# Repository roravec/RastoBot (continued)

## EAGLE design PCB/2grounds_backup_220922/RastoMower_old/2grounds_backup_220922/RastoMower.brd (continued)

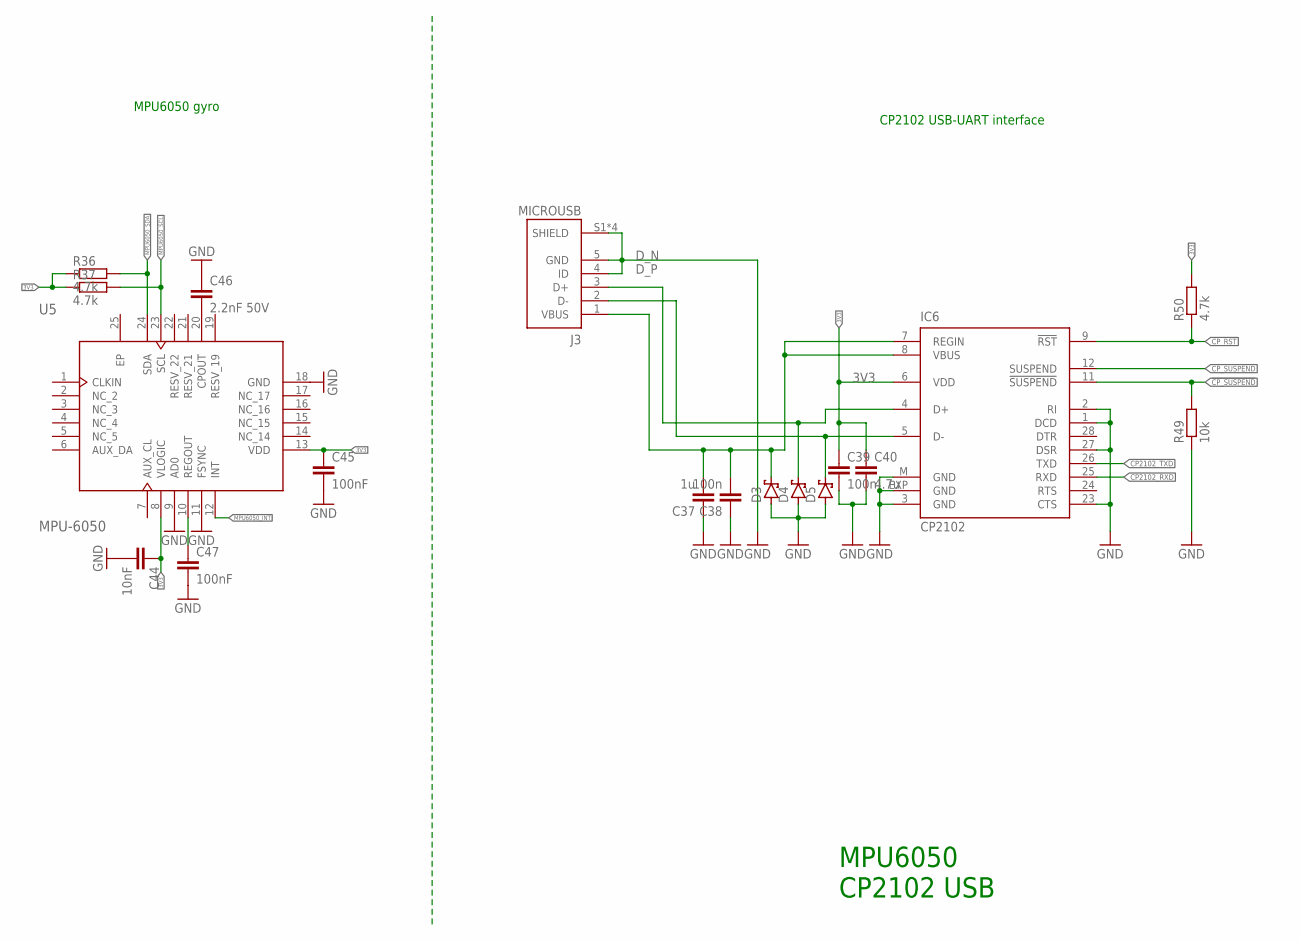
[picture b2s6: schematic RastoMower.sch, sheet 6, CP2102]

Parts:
C37: 1u; C0603
C38, C39: 100n; C0603
C40: 4.7u; C0603
C44: 10nF; C0603
C45, C47: 100nF; C0603
C46: 2.2nF 50V; C0603
D3, D4, D5: BAT60J; SOD323_ST
IC6: CP2102; MLP28
J3: MICROUSB; MOLEX_47642-0001
R36, R37, R50: 4.7k; R0603
R49: 10k; R0603
U5: MPU-6050; 24-VFQFN

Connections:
!CP_SUSPEND: IC6.11 (!SUSPEND), R49.2
CP2102_RXD: IC6.25 (RXD); also elsewhere on the board
CP2102_TXD: IC6.26 (TXD); also elsewhere on the board
CP_RST: IC6.9 (!RST), R50.1
CP_SUSPEND: IC6.12 (SUSPEND)
D_N: D5.C, IC6.5 (D-), J3.2 (D-)
D_P: D4.C, IC6.4 (D+), J3.3 (D+)
EP: U5.25 (EP)
MPU6050_INT: U5.12 (INT)
MPU6050_SCL: R37.2, U5.23 (SCL); also elsewhere on the board
MPU6050_SDA: R36.2, U5.24 (SDA); also elsewhere on the board
unnamed: C37.2, C38.2, D3.C, IC6.7 (REGIN), IC6.8 (VBUS), J3.1 (VBUS)
unnamed: C46.2, U5.20 (CPOUT)
unnamed: C47.1, U5.10 (REGOUT)

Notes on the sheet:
MPU6050 CP2102 USB
MPU6050 gyro
CP2102 USB-UART interface

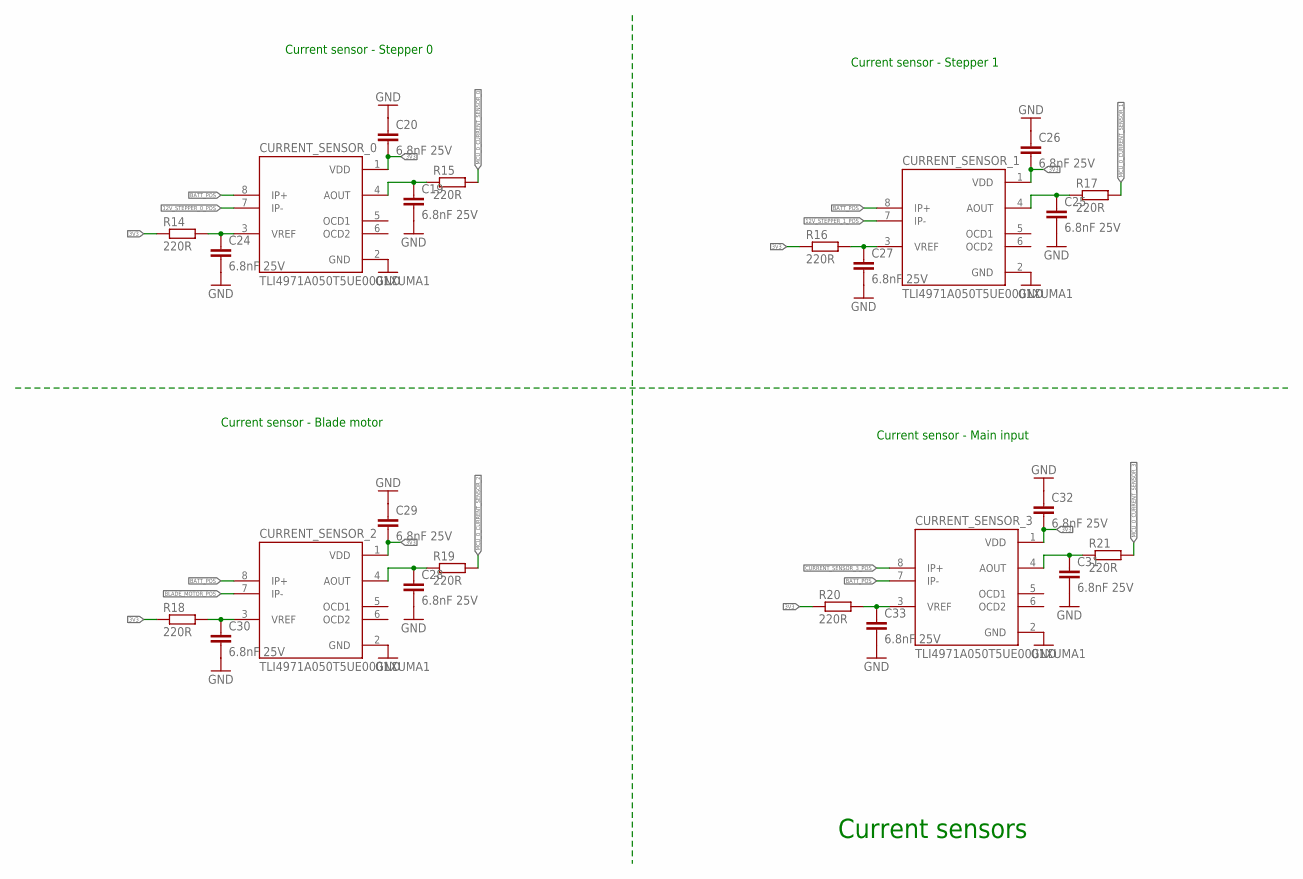
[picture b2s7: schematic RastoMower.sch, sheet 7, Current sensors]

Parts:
C19, C20, C24, C25, C26, C27, C28, C29, C30, C31, C32, C33: 6.8nF 25V; C0603
CURRENT_SENSOR_0, CURRENT_SENSOR_1, CURRENT_SENSOR_2, CURRENT_SENSOR_3: TLI4971A050T5UE0001XUMA1; IC_TLI4971A050T5UE0001XUMA1
R14, R15, R16, R17, R18, R19, R20, R21: 220R; R0805

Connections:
12V_STEPPER_0_POS: CURRENT_SENSOR_0.7 (IP-); also elsewhere on the board
12V_STEPPER_1_POS: CURRENT_SENSOR_1.7 (IP-); also elsewhere on the board
BLADE_MOTOR_POS: CURRENT_SENSOR_2.7 (IP-); also elsewhere on the board
CURRENT_SENSOR_3_POS: CURRENT_SENSOR_3.8 (IP+); also elsewhere on the board
MCU_0_CURRENT_SENSOR_0: R15.2; also elsewhere on the board
MCU_0_CURRENT_SENSOR_1: R17.2; also elsewhere on the board
MCU_0_CURRENT_SENSOR_2: R19.2; also elsewhere on the board
MCU_0_CURRENT_SENSOR_3: R21.2; also elsewhere on the board
unnamed: C19.1, CURRENT_SENSOR_0.4 (AOUT), R15.1
unnamed: C27.1, CURRENT_SENSOR_1.3 (VREF), R16.2
unnamed: C25.1, CURRENT_SENSOR_1.4 (AOUT), R17.1
unnamed: C24.1, CURRENT_SENSOR_0.3 (VREF), R14.2
unnamed: C30.1, CURRENT_SENSOR_2.3 (VREF), R18.2
unnamed: C28.1, CURRENT_SENSOR_2.4 (AOUT), R19.1
unnamed: C33.1, CURRENT_SENSOR_3.3 (VREF), R20.2
unnamed: C31.1, CURRENT_SENSOR_3.4 (AOUT), R21.1

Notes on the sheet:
Current sensors
Current sensor - Stepper 0
Current sensor - Stepper 1
Current sensor - Blade motor
Current sensor - Main input

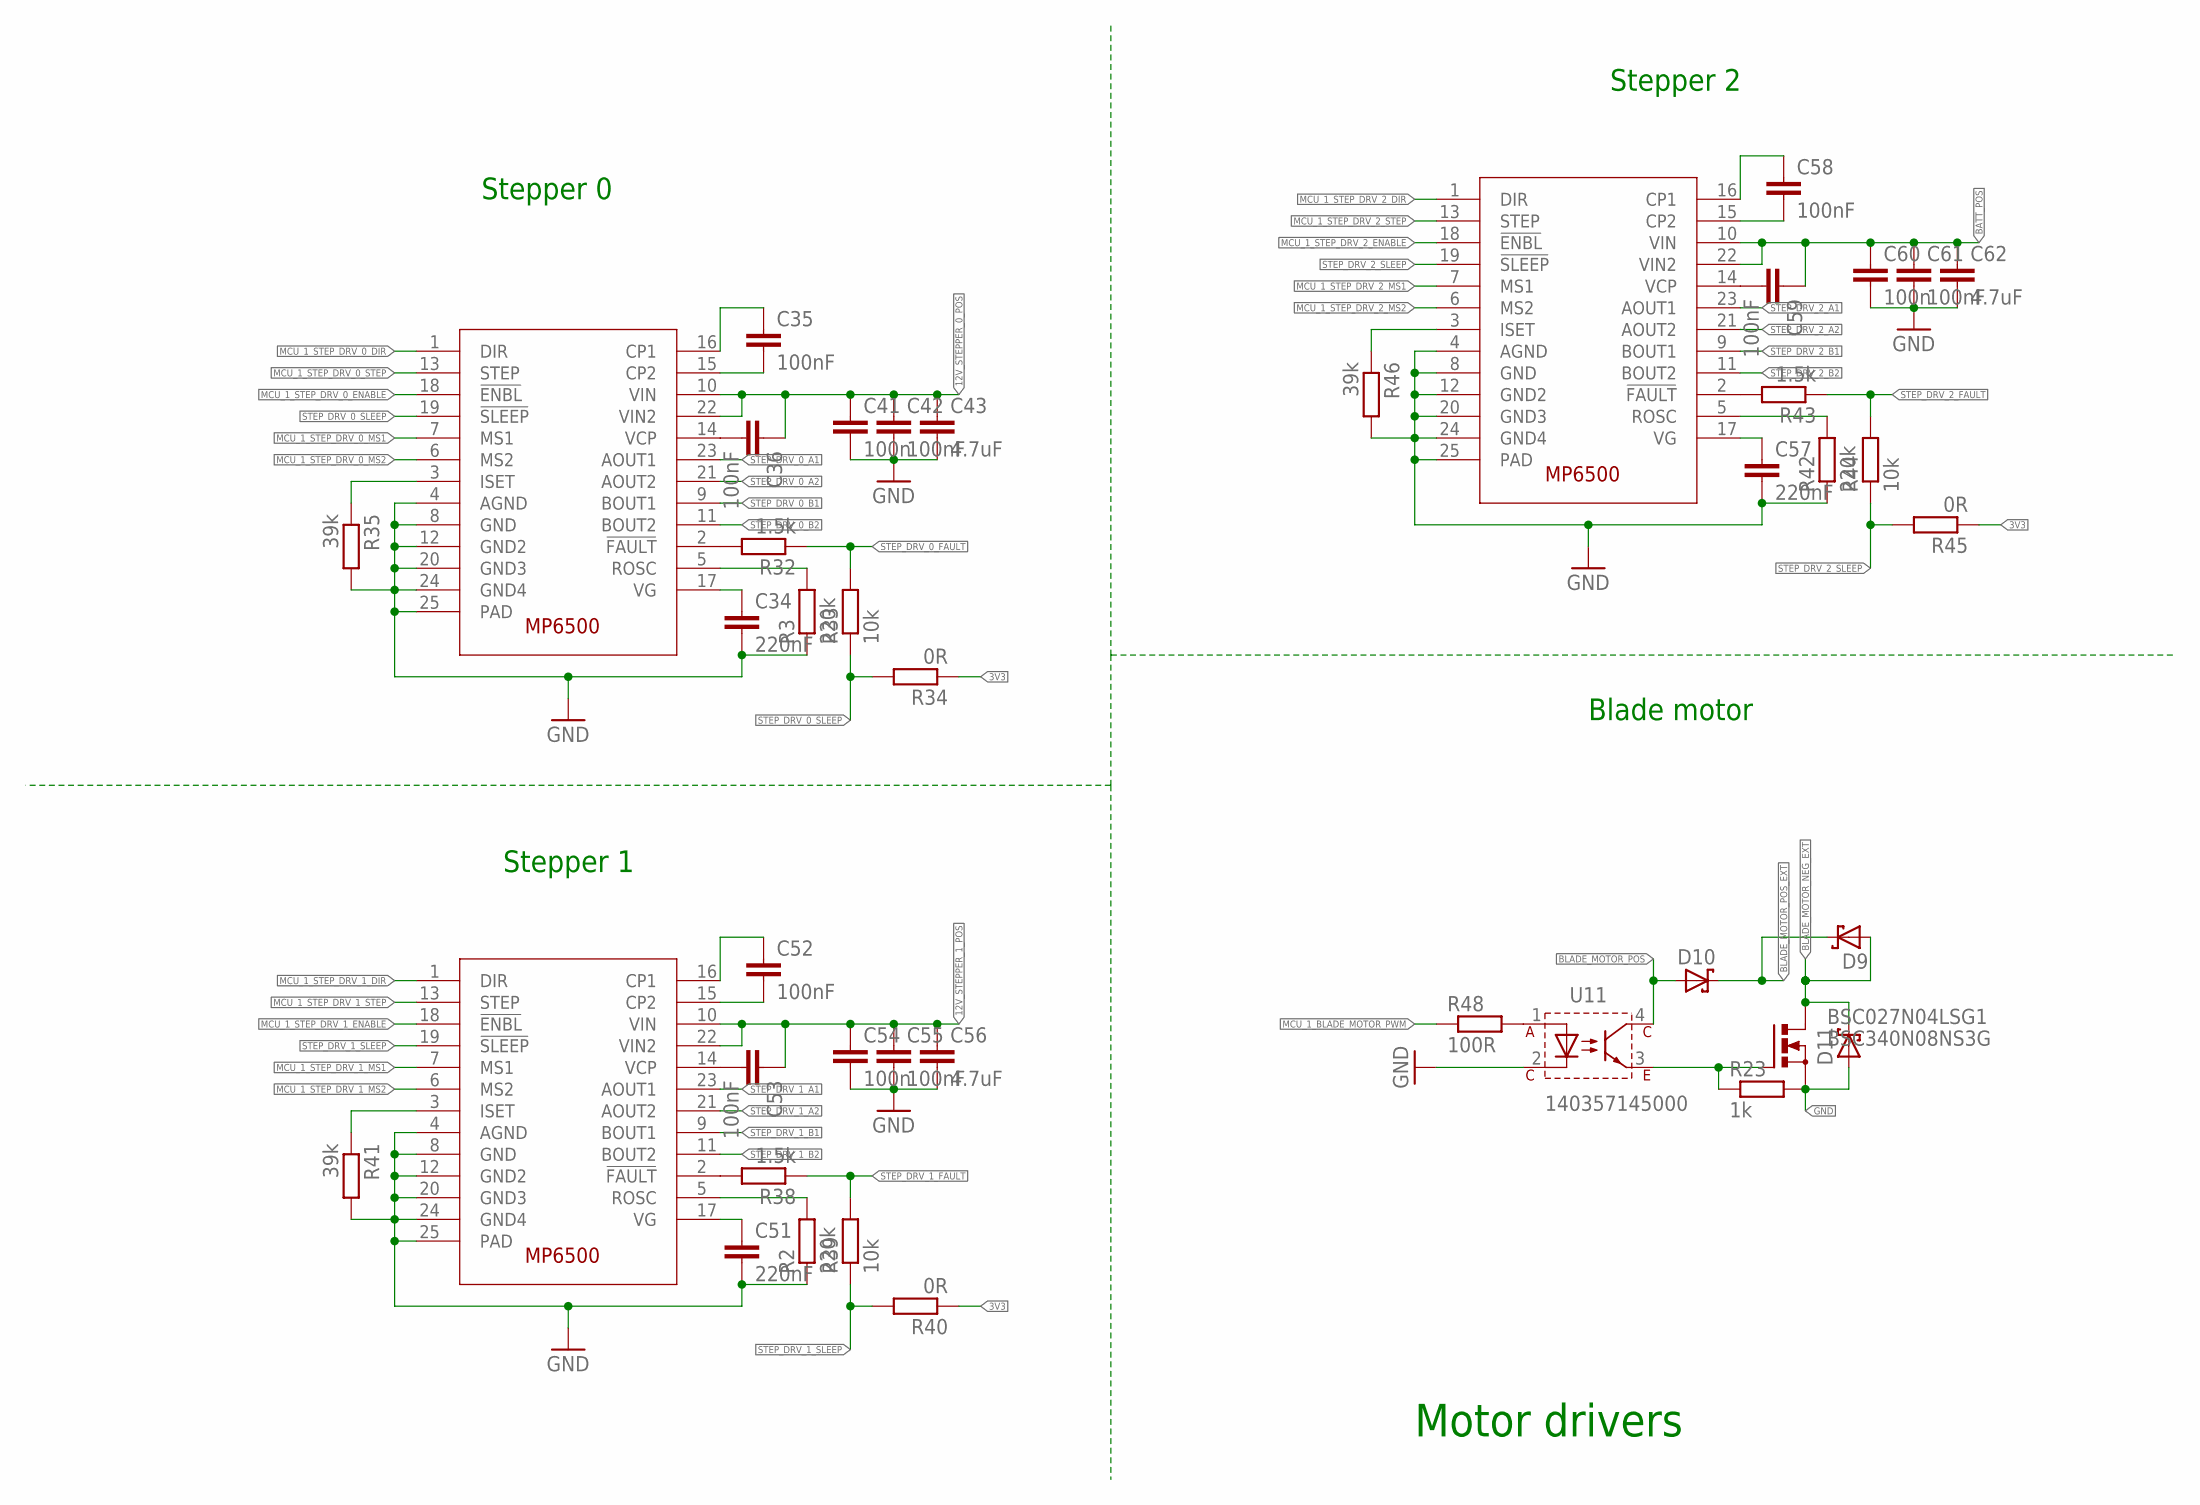
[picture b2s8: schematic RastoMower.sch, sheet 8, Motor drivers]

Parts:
BSC027N04LSG1: BSC340N08NS3G; PG-TDSON-8
C34, C51, C57: 220nF; C0603
C35, C36, C42, C52, C53, C55, C58, C59, C61: 100nF; C0603
C41, C54, C60: 100n; C0603
C43, C56, C62: 4.7uF; C0603
D9, D10, D11: SCHOTTKY-DIODEAG; AG
R2, R3, R42: 220k; R0603
R23: 1k; R0805
R32, R38, R43: 1.5k; R0603
R33, R39, R44: 10k; R0603
R34, R40, R45: 0R; R0603
R35, R41, R46: 39k; R0603
R48: 100R; R0805
U11: 140357145000; WL-OCPT_SOP4
U$1, U$2, U$3: MP6500; QFN65P500X500X100-25N

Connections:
12V_STEPPER_0_POS: C36.1, C41.1, C42.1, C43.1, U$1.10 (VIN), U$1.22 (VIN2); also elsewhere on the board
12V_STEPPER_1_POS: C53.1, C54.1, C55.1, C56.1, U$2.10 (VIN), U$2.22 (VIN2); also elsewhere on the board
BLADE_MOTOR_NEG_EXT: BSC027N04LSG1.5 (D), BSC027N04LSG1.6 (D), BSC027N04LSG1.7 (D), BSC027N04LSG1.8 (D), D9.A, D11.C; also elsewhere on the board
BLADE_MOTOR_POS: D10.A, U11.4; also elsewhere on the board
BLADE_MOTOR_POS_EXT: D9.C, D10.C; also elsewhere on the board
MCU_1_BLADE_MOTOR_PWM: R48.1; also elsewhere on the board
MCU_1_STEP_DRV_0_DIR: U$1.1 (DIR); also elsewhere on the board
MCU_1_STEP_DRV_0_ENABLE: U$1.18 (!ENBL); also elsewhere on the board
MCU_1_STEP_DRV_0_MS1: U$1.7 (MS1); also elsewhere on the board
MCU_1_STEP_DRV_0_MS2: U$1.6 (MS2); also elsewhere on the board
MCU_1_STEP_DRV_0_STEP: U$1.13 (STEP); also elsewhere on the board
MCU_1_STEP_DRV_1_DIR: U$2.1 (DIR); also elsewhere on the board
MCU_1_STEP_DRV_1_ENABLE: U$2.18 (!ENBL); also elsewhere on the board
MCU_1_STEP_DRV_1_MS1: U$2.7 (MS1); also elsewhere on the board
MCU_1_STEP_DRV_1_MS2: U$2.6 (MS2); also elsewhere on the board
MCU_1_STEP_DRV_1_STEP: U$2.13 (STEP); also elsewhere on the board
MCU_1_STEP_DRV_2_DIR: U$3.1 (DIR); also elsewhere on the board
MCU_1_STEP_DRV_2_ENABLE: U$3.18 (!ENBL); also elsewhere on the board
MCU_1_STEP_DRV_2_MS1: U$3.7 (MS1); also elsewhere on the board
MCU_1_STEP_DRV_2_MS2: U$3.6 (MS2); also elsewhere on the board
MCU_1_STEP_DRV_2_STEP: U$3.13 (STEP); also elsewhere on the board
unnamed: C34.1, U$1.17 (VG)
unnamed: R3.2, U$1.5 (ROSC)
unnamed: R48.2, U11.1
unnamed: BSC027N04LSG1.4 (G), R23.1, U11.3
unnamed: C35.2, U$1.15 (CP2)
unnamed: C35.1, U$1.16 (CP1)
unnamed: R32.2, U$1.2 (!FAULT)
unnamed: C36.2, U$1.14 (VCP)
unnamed: C51.1, U$2.17 (VG)
unnamed: R35.1, U$1.3 (ISET)
unnamed: R2.2, U$2.5 (ROSC)
unnamed: C52.2, U$2.15 (CP2)
unnamed: C52.1, U$2.16 (CP1)
unnamed: C53.2, U$2.14 (VCP)
unnamed: R41.1, U$2.3 (ISET)
unnamed: R38.2, U$2.2 (!FAULT)
unnamed: C57.1, U$3.17 (VG)
unnamed: R42.2, U$3.5 (ROSC)
unnamed: C58.2, U$3.15 (CP2)
unnamed: C58.1, U$3.16 (CP1)
unnamed: C59.2, U$3.14 (VCP)
unnamed: R46.1, U$3.3 (ISET)
unnamed: R43.2, U$3.2 (!FAULT)
STEP_DRV_0_A1: U$1.23 (AOUT1); also elsewhere on the board
STEP_DRV_0_A2: U$1.21 (AOUT2); also elsewhere on the board
STEP_DRV_0_B1: U$1.9 (BOUT1); also elsewhere on the board
STEP_DRV_0_B2: U$1.11 (BOUT2); also elsewhere on the board
STEP_DRV_0_FAULT: R32.1, R33.2
STEP_DRV_0_SLEEP: R33.1, R34.2, U$1.19 (!SLEEP)
STEP_DRV_1_A1: U$2.23 (AOUT1); also elsewhere on the board
STEP_DRV_1_A2: U$2.21 (AOUT2); also elsewhere on the board
STEP_DRV_1_B1: U$2.9 (BOUT1); also elsewhere on the board
STEP_DRV_1_B2: U$2.11 (BOUT2); also elsewhere on the board
STEP_DRV_1_FAULT: R38.1, R39.2
STEP_DRV_1_SLEEP: R39.1, R40.2, U$2.19 (!SLEEP)
STEP_DRV_2_A1: U$3.23 (AOUT1); also elsewhere on the board
STEP_DRV_2_A2: U$3.21 (AOUT2); also elsewhere on the board
STEP_DRV_2_B1: U$3.9 (BOUT1); also elsewhere on the board
STEP_DRV_2_B2: U$3.11 (BOUT2); also elsewhere on the board
STEP_DRV_2_FAULT: R43.1, R44.2
STEP_DRV_2_SLEEP: R44.1, R45.2, U$3.19 (!SLEEP)

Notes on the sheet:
Stepper 0
Stepper 1
Stepper 2
Blade motor
Motor drivers

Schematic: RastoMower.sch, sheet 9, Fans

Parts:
BSC027N04LSG3, BSC027N04LSG4, BSC027N04LSG5, BSC027N04LSG6, BSC027N04LSG7: BSC340N08NS3G; PG-TDSON-8
JP10: FAN_0; 1X02
JP11: FAN_1; 1X02
JP12: FAN_2; 1X02
JP13: FAN_3; 1X02
JP25: EMERGENCY LIGHT; 1X02
R22, R51, R52, R53, R119: 200R; R0805
R63, R65, R67, R68, R76: 1k; R0805
U4, U6, U7, U8, U12: 140357145000; WL-OCPT_SOP4

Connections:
MCU_0_EMERGENCY_LIGHT: R119.1; also elsewhere on the board
MCU_0_FAN_0: R22.1; also elsewhere on the board
MCU_0_FAN_1: R51.1; also elsewhere on the board
MCU_0_FAN_2: R53.1; also elsewhere on the board
MCU_0_FAN_3: R52.1; also elsewhere on the board
unnamed: BSC027N04LSG3.4 (G), R68.1, U12.3
unnamed: BSC027N04LSG3.5 (D), BSC027N04LSG3.6 (D), BSC027N04LSG3.7 (D), BSC027N04LSG3.8 (D), JP25.2
unnamed: R119.2, U12.1
unnamed: R22.2, U4.1
unnamed: BSC027N04LSG4.5 (D), BSC027N04LSG4.6 (D), BSC027N04LSG4.7 (D), BSC027N04LSG4.8 (D), JP10.2
unnamed: R51.2, U6.1
unnamed: R52.2, U8.1
unnamed: BSC027N04LSG4.4 (G), R76.1, U4.3
unnamed: BSC027N04LSG5.4 (G), R63.1, U6.3
unnamed: BSC027N04LSG5.5 (D), BSC027N04LSG5.6 (D), BSC027N04LSG5.7 (D), BSC027N04LSG5.8 (D), JP11.2
unnamed: R53.2, U7.1
unnamed: BSC027N04LSG6.4 (G), R65.1, U7.3
unnamed: BSC027N04LSG6.5 (D), BSC027N04LSG6.6 (D), BSC027N04LSG6.7 (D), BSC027N04LSG6.8 (D), JP12.2
unnamed: BSC027N04LSG7.4 (G), R67.1, U8.3
unnamed: BSC027N04LSG7.5 (D), BSC027N04LSG7.6 (D), BSC027N04LSG7.7 (D), BSC027N04LSG7.8 (D), JP13.2

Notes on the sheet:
Fan_0
Fan_1
Fan_2
Fan_3
Fan drivers Emergency light switch
Emergency light

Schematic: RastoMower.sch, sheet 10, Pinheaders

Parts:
BSC027N04LSG2: BSC340N08NS3G; PG-TDSON-8
C63, C64, C65, C66: 1u; C0603
D2: 3V3; SOD80C
JP1: GPS MODULE; 1X05
JP2: STEPPER_0; 1X04
JP3: STEPPER_1; 1X04
JP4: STEPPER_2; 1X04
JP5: LIDAR; 1X08
JP6: RAIN SENSOR; 1X02
JP7: BLADE MOTOR; 1X04
JP8: LIMIT SWITCH UP; 1X02
JP9: LIMIT SWITCH DOWN; 1X02
JP14: TEMP SENSOR 0; 1X03
JP15: TEMP SENSOR 1; 1X03
JP16: TEMP SENSOR 2; 1X03
JP17: TEMP SENSOR 3; 1X03
JP22: PER.WIRE SENSE; 1X04
JP24: PHOTORESISTOR LDR5549; 1X02
JP30: LIMIT_SWITCH_UPPER_MAGNETIC; 1X03
JP31: LIMIT_SWITCH_BOTTOM_MAGNETIC; 1X03
R4, R54: 1k; R0805
R55, R64: 500k; R0805
R56, R58, R59, R60, R107, R108, R109, R110: 10k; R0805
R57, R66: 10R; R0805
R62: 200R; R0805
R69, R70, R71, R72: 5k; R0805
U10: 140357145000; WL-OCPT_SOP4

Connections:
BLADE_MOTOR_NEG_EXT: JP7.3, JP7.4; also elsewhere on the board
BLADE_MOTOR_POS_EXT: JP7.1, JP7.2; also elsewhere on the board
GPS_PPS: JP1.5
GPS_RXD: JP1.4; also elsewhere on the board
GPS_TXD: JP1.3; also elsewhere on the board
LIDAR_RX: JP5.4; also elsewhere on the board
LIDAR_TX: JP5.7; also elsewhere on the board
LIMIT_SWITCH_BOTTOM_MAGNET: R108.1; also elsewhere on the board
LIMIT_SWITCH_BOTTOM_MECHANICAL: R60.1; also elsewhere on the board
LIMIT_SWITCH_UPPER_MAGNET: R107.1; also elsewhere on the board
LIMIT_SWITCH_UPPER_MECHANICAL: R59.1; also elsewhere on the board
MCU_0_LIGHT_SENSOR: R66.1; also elsewhere on the board
MCU_0_TEMP_SENSOR_0: JP14.2, R69.1; also elsewhere on the board
MCU_0_TEMP_SENSOR_1: JP15.2, R70.1; also elsewhere on the board
MCU_0_TEMP_SENSOR_2: JP16.2, R71.1; also elsewhere on the board
MCU_0_TEMP_SENSOR_3: JP17.2, R72.1; also elsewhere on the board
MCU_2_LIDAR_ENABLE: R62.1; also elsewhere on the board
unnamed: JP22.2, R4.2
unnamed: BSC027N04LSG2.5 (D), BSC027N04LSG2.6 (D), BSC027N04LSG2.7 (D), BSC027N04LSG2.8 (D), JP5.5
unnamed: JP8.2, R56.2, R59.2
unnamed: JP9.2, R58.2, R60.2
unnamed: BSC027N04LSG2.4 (G), R54.1, U10.3
unnamed: R62.2, U10.1
unnamed: JP31.2, R108.2, R109.2
unnamed: JP30.2, R107.2, R110.2
PERIMETER_WIRE_SENSE: D2.A, R4.1; also elsewhere on the board
STEP_DRV_0_A1: JP2.1; also elsewhere on the board
STEP_DRV_0_A2: JP2.2; also elsewhere on the board
STEP_DRV_0_B1: JP2.3; also elsewhere on the board
STEP_DRV_0_B2: JP2.4; also elsewhere on the board
STEP_DRV_1_A1: JP3.1; also elsewhere on the board
STEP_DRV_1_A2: JP3.2; also elsewhere on the board
STEP_DRV_1_B1: JP3.3; also elsewhere on the board
STEP_DRV_1_B2: JP3.4; also elsewhere on the board
STEP_DRV_2_A1: JP4.1; also elsewhere on the board
STEP_DRV_2_A2: JP4.2; also elsewhere on the board
STEP_DRV_2_B1: JP4.3; also elsewhere on the board
STEP_DRV_2_B2: JP4.4; also elsewhere on the board

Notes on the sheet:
GPS TXD to MCU RX!
Resistance is between 10M (dry) to less than 1M (fully wet)
Limit switch UP
Limit switch BOTTOM
Blade motor
Stepper_0
Stepper_1
Stepper_2
GPS
Rain sensor
Mechanical limit switches
Temperature sensor DHT11
Perimeter wire sense
Lidar
Magnetic limit switches
Pinheaders
Resistance is between 10M (dark) to less than 100k (daylight)
Light sensor

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
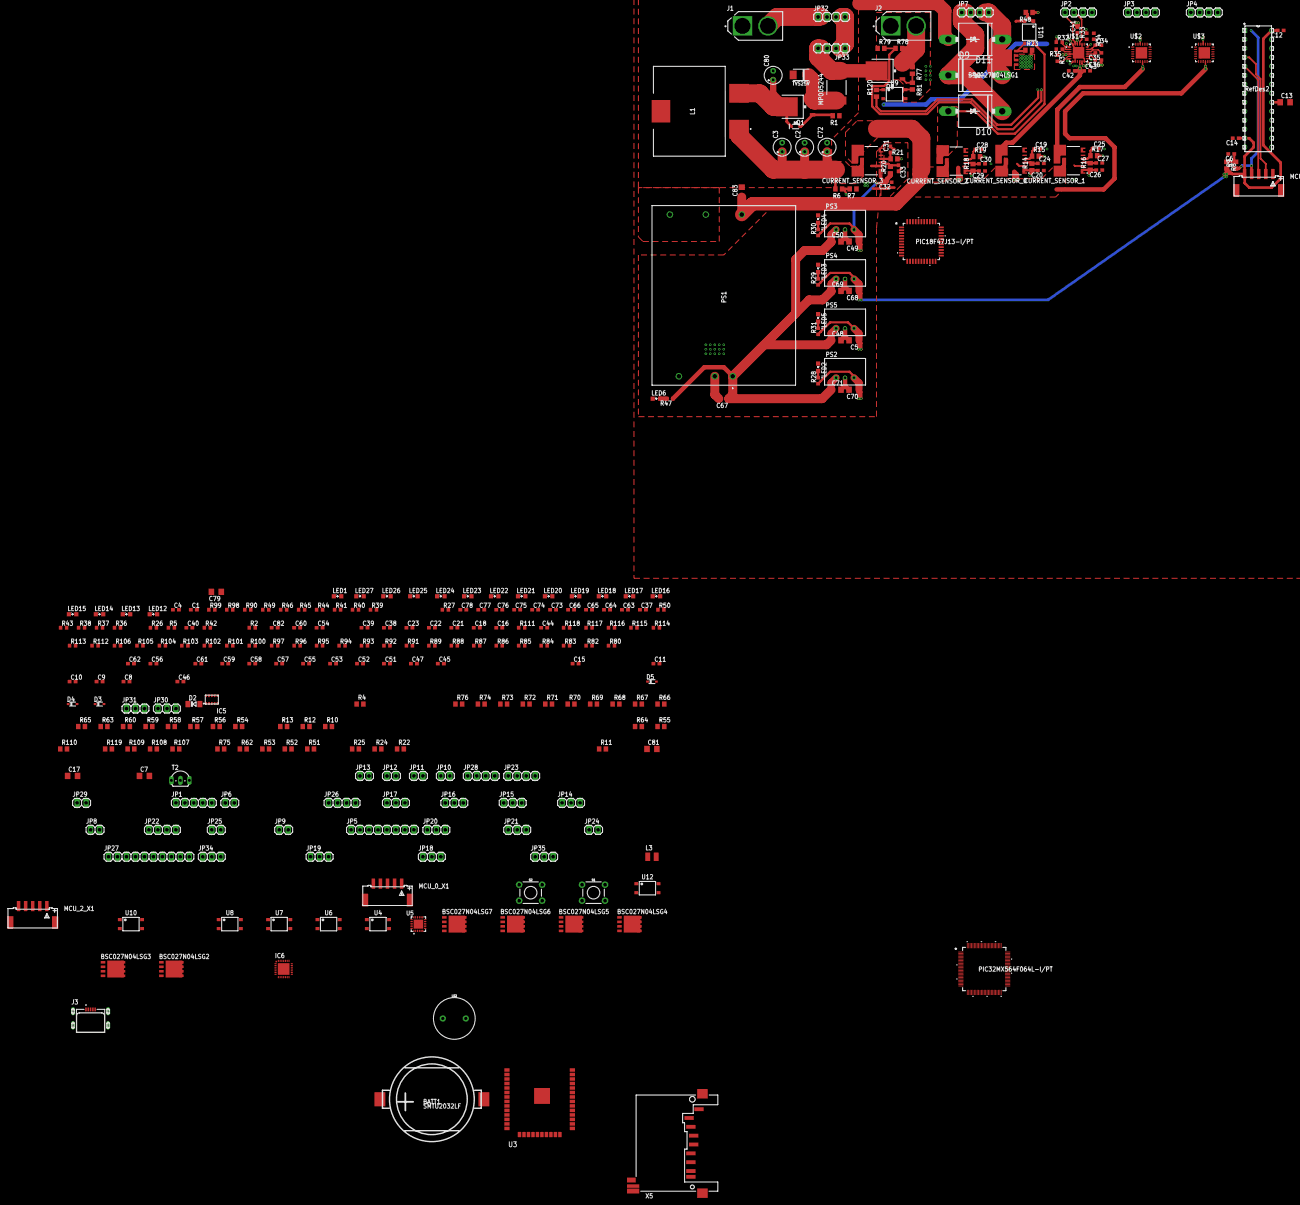
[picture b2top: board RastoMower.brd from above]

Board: 2 copper layers, 319 parts (0 on the bottom side), 242 nets.

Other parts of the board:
LED6: SML0805
PS1: TEN_25-1211; TEN251211
R47: 200R; R0603

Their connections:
unnamed: LED6.A, R47.2

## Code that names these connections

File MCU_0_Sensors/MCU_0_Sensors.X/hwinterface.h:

/* 
 * File:   pins.h
 * Author: orras
 *
 * Created on January 9, 2023, 2:21 PM
 */

#ifndef HWINTERFACE_H
#define	HWINTERFACE_H

#include <xc.h>

/* UART ***********************************/
#define UART_RX_TRIS        TRISCbits.TRISC7
#define UART_TX_TRIS        TRISCbits.TRISC6
/******************************************/ 

/* Power outputs **************************/
#define POWER_OUTPUT_0_TRIS TRISDbits.TRISD4
#define POWER_OUTPUT_0_LAT  LATDbits.LATD4
#define POWER_OUTPUT_0_PORT PORTDbits.RD4
#define POWER_OUTPUT_1_TRIS TRISDbits.TRISD5
#define POWER_OUTPUT_1_LAT  LATDbits.LATD5
#define POWER_OUTPUT_1_PORT PORTDbits.RD5
#define POWER_OUTPUT_2_TRIS TRISDbits.TRISD6
#define POWER_OUTPUT_2_LAT  LATDbits.LATD6
#define POWER_OUTPUT_2_PORT PORTDbits.RD6
#define POWER_OUTPUT_3_TRIS TRISDbits.TRISD7
#define POWER_OUTPUT_3_LAT  LATDbits.LATD7
#define POWER_OUTPUT_3_PORT PORTDbits.RD7
#define POWER_OUTPUT_4_TRIS TRISCbits.TRISC0
#define POWER_OUTPUT_4_LAT  LATCbits.LATC0
#define POWER_OUTPUT_4_PORT PORTCbits.RC0
/******************************************/

/* LEDS ***********************************/
#define LED_0_TRIS          TRISDbits.TRISD0
#define LED_0_LAT           LATDbits.LATD0
#define LED_1_TRIS          TRISDbits.TRISD1
#define LED_1_LAT           LATDbits.LATD1
#define LED_2_TRIS          TRISDbits.TRISD2
#define LED_2_LAT           LATDbits.LATD2
/******************************************/

/* OTHER OUTPUTS **************************/
#define BUZZER_TRIS         TRISCbits.TRISC1
#define BUZZER_LAT          LATCbits.LATC1
/******************************************/

/* TEMP SENSORS ***************************/
#define TEMP_SENSOR_0_TRIS  TRISBbits.TRISB2
#define TEMP_SENSOR_0_LAT   LATBbits.LATB2
#define TEMP_SENSOR_0_PORT  PORTBbits.RB2
#define TEMP_SENSOR_1_TRIS  TRISBbits.TRISB3
#define TEMP_SENSOR_1_LAT   LATBbits.LATB3
#define TEMP_SENSOR_1_PORT  PORTBbits.RB3
#define TEMP_SENSOR_2_TRIS  TRISBbits.TRISB1
#define TEMP_SENSOR_2_LAT   LATBbits.LATB1
#define TEMP_SENSOR_2_PORT  PORTBbits.RB1
#define TEMP_SENSOR_3_TRIS  TRISBbits.TRISB0
#define TEMP_SENSOR_3_LAT   LATBbits.LATB0
#define TEMP_SENSOR_3_PORT  PORTBbits.RB0
/******************************************/

/* DCINPUT SENSORS ************************/
#define EXT_INPUT_SENSE_TRIS    TRISBbits.TRISB5
#define EXT_INPUT_SENSE_PORT    PORTBbits.RB5
#define EXT_INPUT_ENABLE_TRIS   TRISDbits.TRISD3
#define EXT_INPUT_ENABLE_LAT    LATDbits.LATD3
#define BATTERY_STATUS_TRIS     TRISAbits.TRISA2
#define BATTERY_STATUS_AN       AN2
#define BATTERY_STATUS_ANCH     0b0010
/******************************************/

/* CURRENT SENSORS ************************/
#define CURRENT_SENSOR_0_TRIS   TRISAbits.TRISA0
#define CURRENT_SENSOR_0_AN     AN0
#define CURRENT_SENSOR_0_ANCH   0b0000
#define CURRENT_SENSOR_1_TRIS   TRISAbits.TRISA1
#define CURRENT_SENSOR_1_AN     AN1
#define CURRENT_SENSOR_1_ANCH   0b0001
#define CURRENT_SENSOR_2_TRIS   TRISEbits.TRISE0
#define CURRENT_SENSOR_2_AN     AN5
#define CURRENT_SENSOR_2_ANCH   0b0101
#define CURRENT_SENSOR_3_TRIS   TRISEbits.TRISE1
#define CURRENT_SENSOR_3_AN     AN6
#define CURRENT_SENSOR_3_ANCH   0b0110
/******************************************/

/* OTHER ANALOG SENSORS *******************/
#define RAIN_SENSOR_TRIS    TRISEbits.TRISE2
#define RAIN_SENSOR_AN      AN7
#define RAIN_SENSOR_ANCH    0b0111
#define LIGHT_SENSOR_TRIS   TRISAbits.TRISA5
#define LIGHT_SENSOR_AN     AN4
#define LIGHT_SENSOR_ANCH   0b0100
/******************************************/

/* OTHER INPUTS ***************************/
#define TILT_SENSOR_TRIS    TRISCbits.TRISC2
#define TILT_SENSOR_PORT    PORTCbits.RC2
/******************************************/

void HwInterface_Init(void);

/*
0000 = Channel 00 (AN0)
0001 = Channel 01 (AN1)
0010 = Channel 02 (AN2)
0011 = Channel 03 (AN3)
0100 = Channel 04 (AN4)
0101 = Channel 05 (AN5)(1)
0110 = Channel 06 (AN6)(1)
0111 = Channel 07 (AN7)(1)
1000 = Channel 08 (AN8)
1001 = Channel 09 (AN9)
1010 = Channel 10 (AN10)
1011 = Channel 11 (AN11)
1100 = Channel 12 (AN12)*/

#endif	/* HWINTERFACE_H */

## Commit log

2023-01-09 Init
2023-01-09 Init2
2023-01-09 Init3
2023-01-10 DHT11 works
2023-01-16 MCU0 work
2023-01-18 Rarray + ERMA comm protocol
2023-01-18 MCU_0 is ready for testing
2023-01-19 MCU0 testing
2023-01-20 MCU1_Motors work
2023-01-20 MCU1 work
2023-01-22 ErmaCommProtocol changes
2023-01-23 Motors speed control
2023-01-24 MCU1_Commands in progress
2023-01-25 MCU1 message actions
2023-01-26 MCU2 work start
2023-01-27 ECP fixed data len
2023-01-29 Control panel
2023-01-30 DMA work in progress
2023-01-31 DMA work in progress 2
2023-01-31 ESP32 UART work in progress
2023-02-01 MCU2 work in progress
2023-02-02 DMA in progress 2
2023-02-04 DMA UART work in progress
2023-02-05 DMA UART works
2023-02-07 I2C work in progress
2023-02-08 MPU6050 in progress
2023-02-10 MPU6050 works
2023-02-12 Compass works
2023-02-13 Documentation and PCB added
2023-02-20 Lidar
2023-02-20 DMA transfer MCU2 to MCU3
2023-02-22 GPS baudrate fix
2023-02-24 DMA MCU2 to MCU3 fixed
2023-02-28 ControlPanel app work in progress
2023-03-03 ECP fixes
2023-03-05 MCU3 to MCU2 commands
2023-03-06 MCU3 to MCU0 commands
2023-03-07 Bugfixes
2023-03-28 Control panel v1
2023-03-29 Reference run, ESP32 webserver, Control panel
2023-03-30 ControlPanel - +gyro
2023-04-01 Steppers in move signal
